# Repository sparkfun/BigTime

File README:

BigTime is an open source hardware kit that allows the user to build their own watch.

The hardware design is released under CC-SA v3 license.
The firmware is released under a modified beerware license.

This project is forked with permission from Spikenzie labs' Solder:Time kit that is not open source. We really wanted to make the watch kits easier to hack so we combine the two ICs (a PIC and an RTC) into one (the ATmega328). We also rewrote all the code in C/Arduino so that it is easier to maintain and hack. We also reduced the current consumption so that you should get an estimated 2 years of run time on a single CR2032 cell!

v1.0 Initial code release 7-17-2011
v1.1 Added rough support for other display colors 8-19-2011

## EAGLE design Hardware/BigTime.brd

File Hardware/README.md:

# What Are these Files?

The .sch and .brd files hare are Eagle CAD schematic and PCB design files.

These files were created with Eagle 6.2.0. There is a free, lite, version of Eagle available from [cadsoftusa.com](cadsoftusa.com).

# License
This product is open source! These Eagle files are released under the Creative Commons Share-Alike Attribution license ([CC BY-SA 3.0](http://creativecommons.org/licenses/by-sa/3.0/us/)).
Please use, reuse, and modify these files as you see fit. Please maintain attribution and release anything derivative under the same license.

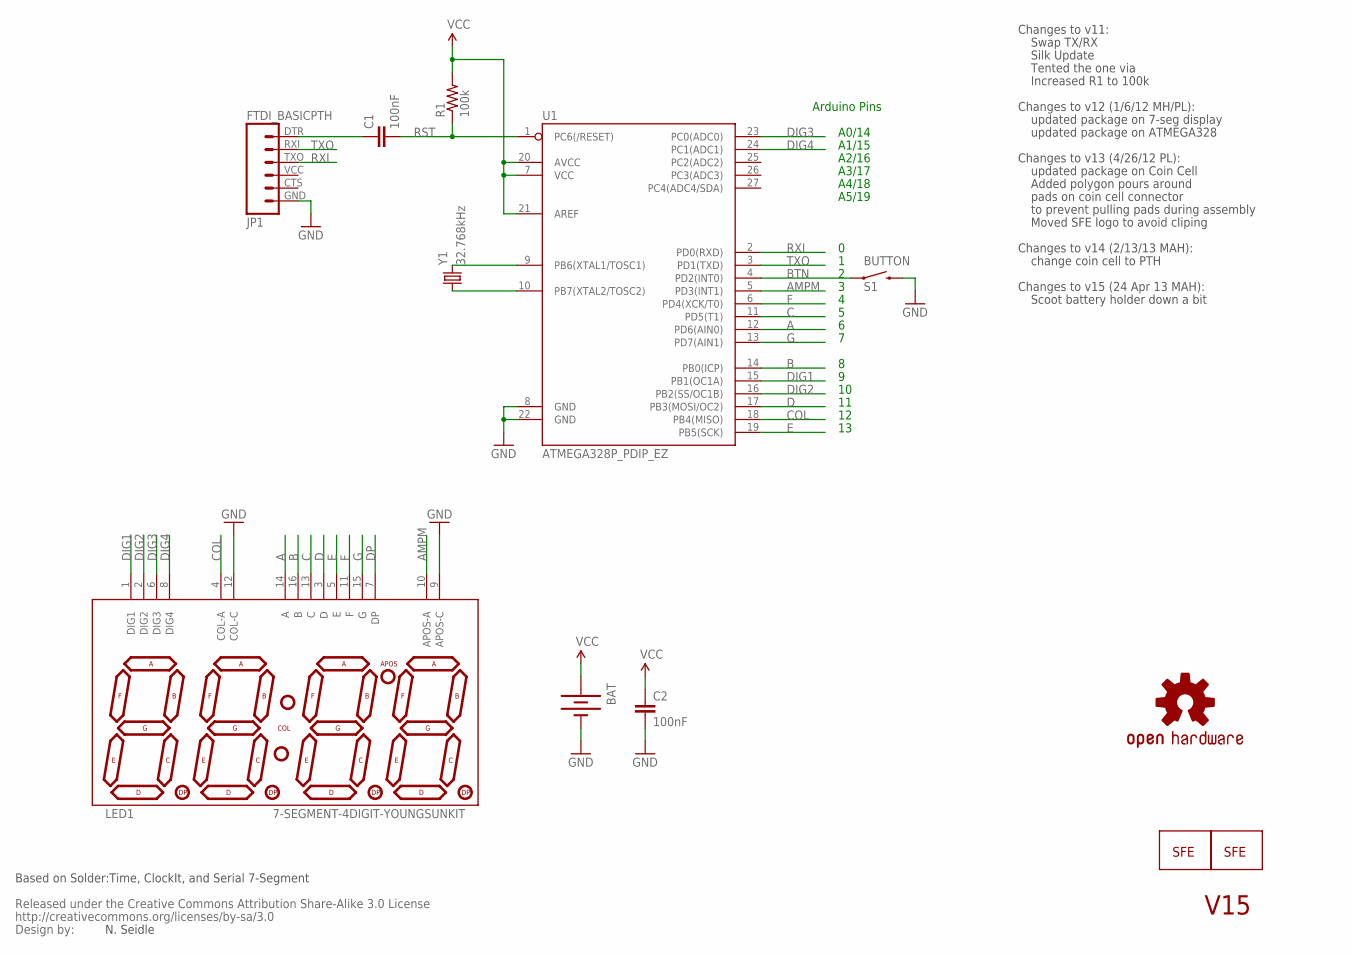
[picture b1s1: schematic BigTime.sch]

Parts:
BAT: BATTERYFOB; BATTERY_20MM_PTH_COMPACT
C1, C2: 100nF; CAP-PTH-SMALLEZ
JP1: FTDI_BASICPTH; FTDI_BASIC
LED1: 7-SEGMENT-4DIGIT-YOUNGSUNKIT; 7-SEGMENT-4DIGIT-YOUNGSUN-KIT
R1: 100k; AXIAL-0.3-KIT
S1: BUTTON; TACTILE-PTH-SIDEEZ
U1: ATMEGA328P_PDIP_EZ; DIL28-EZ
U$1: LOGO-SFESK; SFE-LOGO-FLAME
U$2: CREATIVE_COMMONS
U$4: OSHW-LOGOS; OSHW-LOGO-S
U$5: LOGO-SFENW2; SFE-NEW-WEB
Y1: 32.768kHz; TC26HEZ

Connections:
A: LED1.14 (A), U1.12 (PD6(AIN0))
AMPM: LED1.10 (APOS-A), U1.5 (PD3(INT1))
B: LED1.16 (B), U1.14 (PB0(ICP))
BTN: S1.1, U1.4 (PD2(INT0))
C: LED1.13 (C), U1.11 (PD5(T1))
COL: LED1.4 (COL-A), U1.18 (PB4(MISO))
D: LED1.3 (D), U1.17 (PB3(MOSI/OC2))
DIG1: LED1.1 (DIG1), U1.15 (PB1(OC1A))
DIG2: LED1.2 (DIG2), U1.16 (PB2(SS/OC1B))
DIG3: LED1.6 (DIG3), U1.23 (PC0(ADC0))
DIG4: LED1.8 (DIG4), U1.24 (PC1(ADC1))
DP: LED1.7 (DP)
E: LED1.5 (E), U1.19 (PB5(SCK))
F: LED1.11 (F), U1.6 (PD4(XCK/T0))
G: LED1.15 (G), U1.13 (PD7(AIN1))
GND: BAT.2 (-), C2.2, JP1.GND (6), LED1.9 (APOS-C), LED1.12 (COL-C), S1.2, U1.8 (GND), U1.22 (GND)
unnamed: U1.10 (PB7(XTAL2/TOSC2)), Y1.1
unnamed: U1.9 (PB6(XTAL1/TOSC1)), Y1.2
unnamed: C1.1, JP1.DTR (1)
RST: C1.2, R1.P$1 (1), U1.1 (PC6(/RESET))
RXI: JP1.TXO (3), U1.2 (PD0(RXD))
TXO: JP1.RXI (2), U1.3 (PD1(TXD))
VCC: BAT.1 (+), C2.1, R1.P$2 (2), U1.7 (VCC), U1.20 (AVCC), U1.21 (AREF)

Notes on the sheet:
N. Seidle
A0/14
A1/15
A2/16
A3/17
A4/18
A5/19
Arduino Pins
Based on Solder:Time, ClockIt, and Serial 7-Segment
Changes to v11:
Swap TX/RX
Silk Update
Tented the one via
Increased R1 to 100k
Changes to v12 (1/6/12 MH/PL):
updated package on 7-seg display
updated package on ATMEGA328
Changes to v13 (4/26/12 PL):
Added polygon pours around
pads on coin cell connector
to prevent pulling pads during assembly
updated package on Coin Cell
Moved SFE logo to avoid cliping
Changes to v14 (2/13/13 MAH):
change coin cell to PTH
V15
Changes to v15 (24 Apr 13 MAH):
Scoot battery holder down a bit

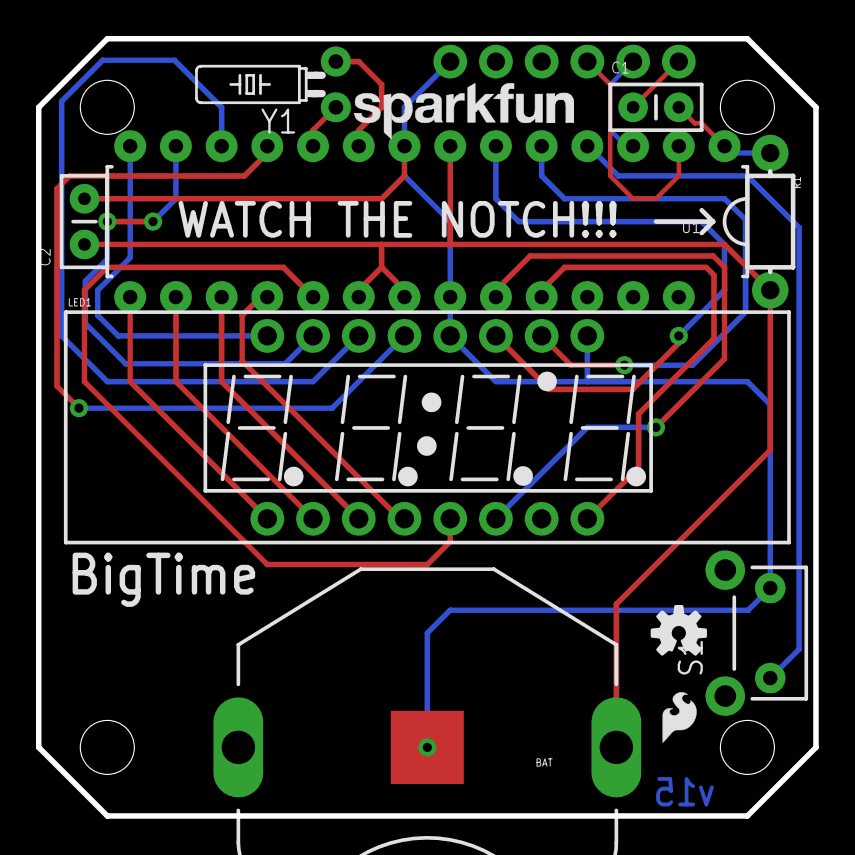
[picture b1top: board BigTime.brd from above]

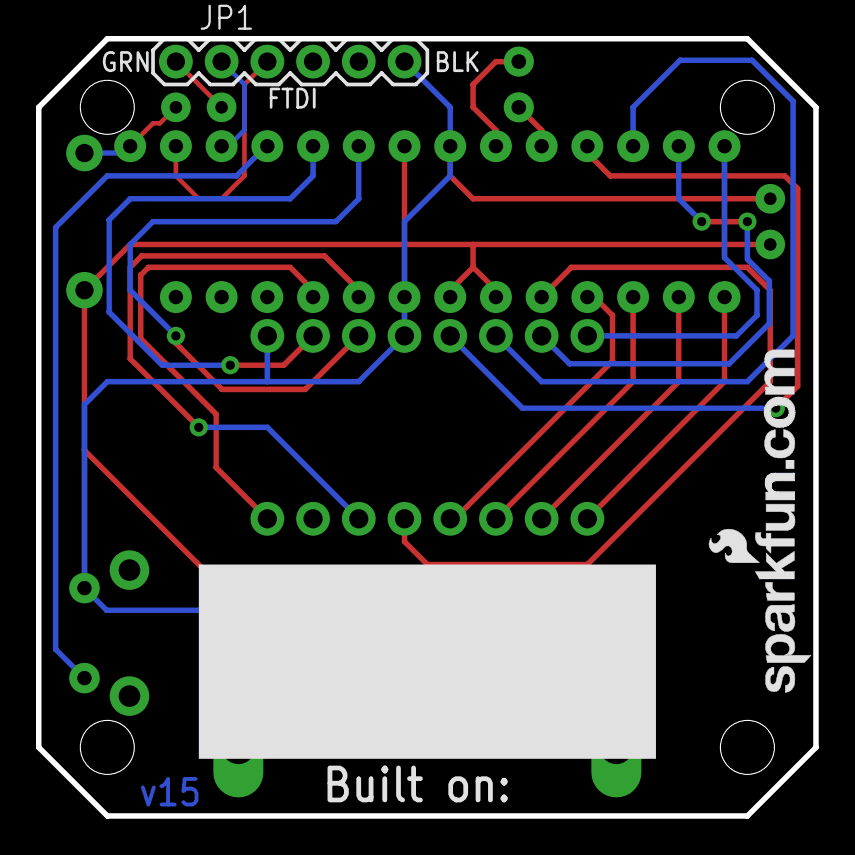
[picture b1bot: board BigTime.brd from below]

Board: 2 copper layers, 43.2 x 43.2 mm, 14 parts (2 on the bottom side), 22 nets.

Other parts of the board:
U$3: LOGO-SFENEW; SFE-NEW-WEBLOGO

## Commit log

2011-11-09 Initial commit at v1.1. Added display strings (for example "bLuE").
2011-11-09 Corrected typos.
2012-07-15 Added TV-B-Gone code. Added enclosure file.
    I added the TV-B-Gone off codes to the main file. Works fairly well.
    Distance is only 5-10 feet. It takes 20-25 seconds to broadcast all the
    IR codes.
    Added enclosure file. Enclosure was modified to have a spot for the IR
    LED on layer 3. Layer 2 was increased in thickness by 1.5mm to allow for
    more solder joint height. Old versions required users to cut the solder
2012-07-15 Added CC license to svg file.
2012-07-19 Removed TV-B-Gone by default. Re-enable via define.
2012-07-19 Added debounce after interrupt wake up.
2013-02-12 No files changed from last committed version- purely a change to the directory structure to reflect our current standards.
2013-02-13 Revert "No files changed from last committed version- purely a change to"
    This reverts commit b4c4fb3299e3d308940143aaff8a9bb41b551c22.
2013-02-13 Update files to v13 (most recent production files) Update tree to SparkFun standard
2013-02-13 Mods for threaded inserts, PTH battery holder. - Modified .sch and .brd files to V13 to add PTH battery holder. - Modified enclosure file to change thickness of layer 1 and hole sizes on layer 1 to 3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
2013-03-06 porting readme to markdown and prettyfying
2013-03-07 some additional readme cleanup for consistency with other cleaned SFE readmes
2013-04-22 Repo organization clean up
2013-04-22 Additional README updates and structure cleaning
2013-04-24 Tweaks to board, enclosure, repo - Enclosure: * Hole size in layer 1 is now right for threaded inserts * Change thickness note on layers 2 and 3 to 1/8" * Moved lever from center of layer 3 to ensure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
2013-06-25 Modified enclosure so PTH batt holder fits
2013-09-09 Fixing board files to v15 So, the wild divergence between the two branches caused some... issues...during merging. The files in the repository now should be representative of production.
2013-10-08 Fixed firmware directory structure. As it was, files would not compile in Arduino.
2013-10-12 Update BigTime.ino
    Hacked to be used with one seven-segment display.
2021-06-05 release TV B Gone
2025-06-27 Update README.md
    Updating link

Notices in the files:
parts and their libraries:
SparkFun: Released under the Creative Commons Attribution Share-Alike 3.0 License
SparkFun-DigitalIC: Licensing: CC v3.0 Share-Alike You are welcome to use this library for commercial purposes.
